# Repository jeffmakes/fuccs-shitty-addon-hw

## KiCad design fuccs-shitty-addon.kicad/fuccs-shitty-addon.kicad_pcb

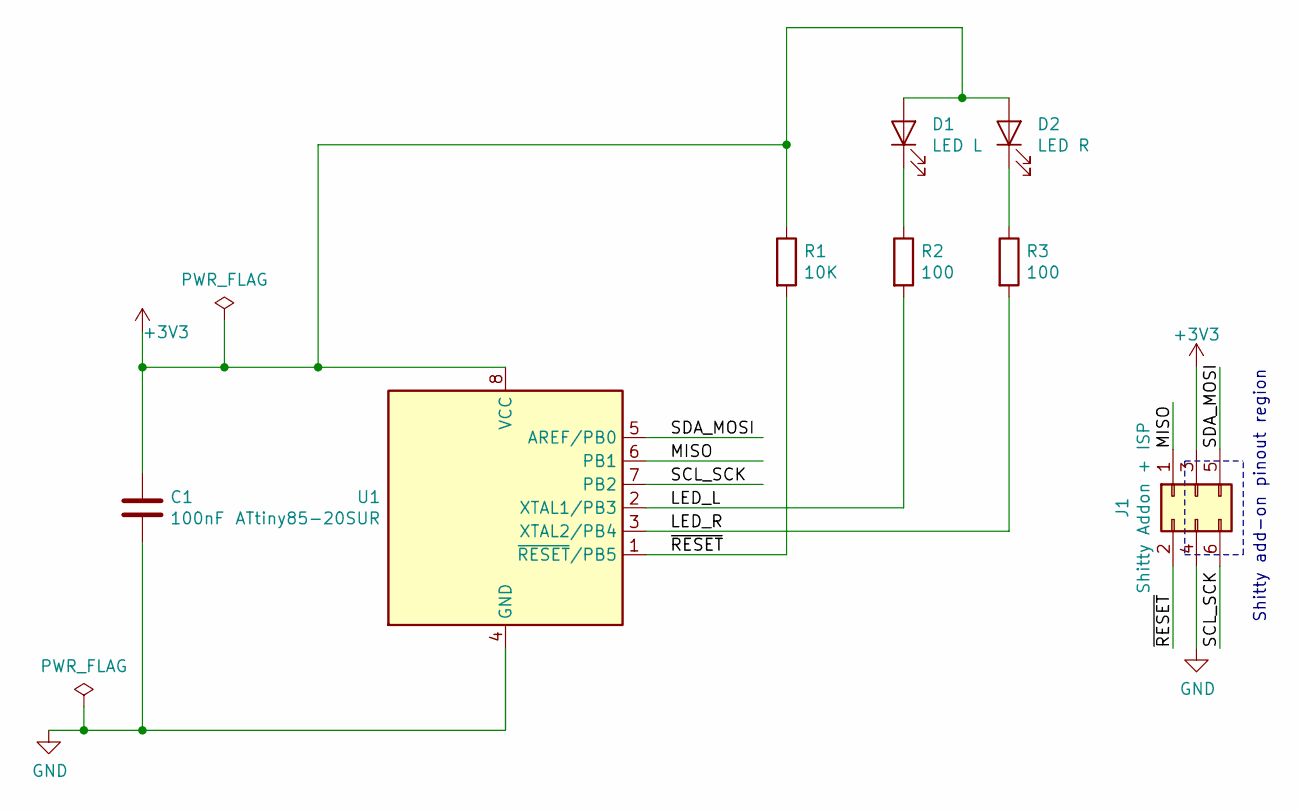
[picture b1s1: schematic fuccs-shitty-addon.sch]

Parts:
C1: 100nF; C_0805_HandSoldering
D1: LED L; LED_TOPLED-Reverse-Gullwing_Handsoldering
D2: LED R; LED_TOPLED-Reverse-Gullwing_Handsoldering
J1: Shitty Addon + ISP; Pin_Header_Straight_2x03_Pitch2.54mm_SMD_no-silk
R1: 10K; R_0805_HandSoldering
R2, R3: 100; R_0805_HandSoldering
U1: ATtiny85-20SUR; SOIJ-8_5.3x5.3mm_Pitch1.27mm

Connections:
+3V3: C1.1, D1.2 (A), D2.2 (A), J1.3, R1.1, U1.8 (VCC)
/LED_L: R2.2, U1.2 (XTAL1/PB3)
/LED_R: R3.2, U1.3 (XTAL2/PB4)
/MISO: J1.1, U1.6 (PB1)
/SCL_SCK: J1.6, U1.7 (PB2)
/SDA_MOSI: J1.5, U1.5 (AREF/PB0)
/~RESET~: J1.2, R1.2, U1.1 (~RESET~/PB5)
GND: C1.2, J1.4, U1.4 (GND)
unnamed: D1.1 (K), R2.1
unnamed: D2.1 (K), R3.1

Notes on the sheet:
Shitty add-on pinout region

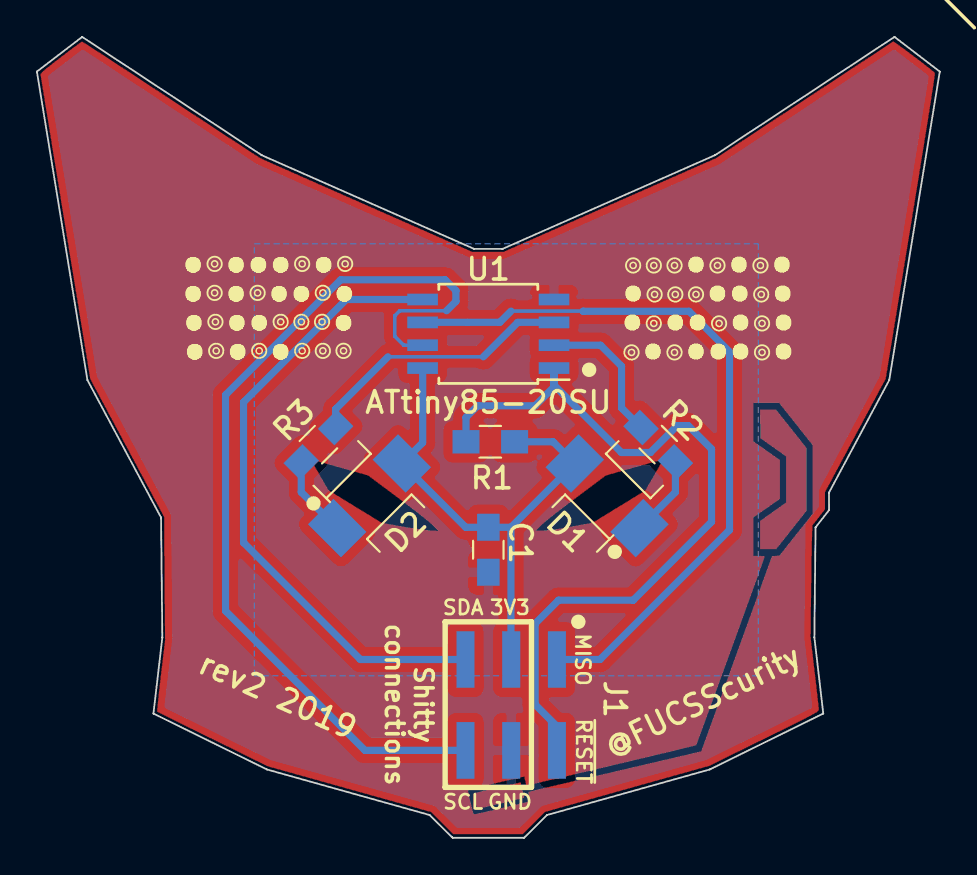
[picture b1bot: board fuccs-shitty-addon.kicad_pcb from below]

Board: 2 copper layers, 50.2 x 44.5 mm, 8 parts (8 on the bottom side), 10 nets.

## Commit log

2019-03-10 Create an emptyu Kicad project around the fuccs graphic exported from SVG via SVG2Shenzhen
2019-03-11 Rotate connector pinout to make it more obvious which pins are the SA pins. Label tracks, tidy up schematic, and point the LED footprints at a local footprint lib
2019-03-11 gitignore
2019-03-11 local libs include
2019-03-11 Increase clearance between pads and pcb hole
2019-03-11 Components placed
2019-03-11 gitignore netlist
2019-03-11 Routing complete
2019-03-11 Pin header variant without silk
2019-03-11 Fix layer alignment and weird artefacts miles outside the board perimeter
2019-03-11 Gerbers released for production
2019-03-11 Fabrication README
2019-03-13 Add FUCCS handle to bottom silk
2019-03-17 Add tick marks to silk to aid LED alignment. Unfortunately cannot add keepouts to footprints
2019-03-17 Reroute track out of keepout region. Add keepouts. Add pin labels for the MISO and RESET signals, bump revision number
2019-03-17 Add mask window under LED firing region
2019-03-17 Mask windows under LED's
2019-03-17 Generate gerbers
2019-03-18 Update fabrication notes
2019-03-18 Gerbers released for rev2 fabrication
